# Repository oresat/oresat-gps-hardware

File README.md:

# oresat-gps-hardware 

## Overview

This is the repo for our OreSat GPS Card. For software, see the [oresat-gps-software](https://github.com/oresat/oresat-gps-software) repo.

The card has two GPS receivers on it:

* A [**SkyTraq Orion-B16** GNSS module](https://navspark.mybigcommerce.com/12mm-x-16mm-gnss-receiver-module-for-leo-applications/), a GNSS receiver module meant for university CubeSat use.
* An [Analog Devices MAX2771 SDR GNSS receiver IC](https://www.analog.com/en/products/max2771.html) that is read by the [Octavo OSD335x-SM processor's](https://octavosystems.com/octavo_products/osd335x-sm/) PRU and then parsed using the [GNSS-SDR project](https://gnss-sdr.org/) software.

## Status

TRL 6-7 ish. Flown, but not yet demonstrated to work in space.

* v1.1: Assembled, electrical and software test out, Orion not yet locked and demonstrated to work. MAX not yet tested.
* v1.0: Works: SkyTraq confirmed locked on ground. SDR datastream captured, and processed, but this software seems to be lost to the sands of time? Flown on OreSat0 but never turned on due to comms issues with OreSat0.

## License

All materials in this repo are copyright Portland State Aerospace Society and are licensed under the CERN Open Hardware Licence Version 2 -
Strongly Reciprocal (CERN-OHL-S v2), or any later version. A copy of the license is located in [here](LICENSE.md).

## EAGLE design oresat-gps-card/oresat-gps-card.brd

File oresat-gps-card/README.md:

---
title: "**OreSat GPS Card**"
subtitle: |
  **Fabrication and Assembly Information**\
  For build TIME-STAMP
fontsize: 10pt
geometry:
  - margin=0.5in
toc: true
toc-depth: 2
colorlinks: true
urlcolor: blue
---

\newpage

# About this Board

## Board Description

The OreSat GPS Card provides two GPS receivers for the OreSat bus:

1. The SkyTraq Orion B16 which is a COTS GPS receiver capable of lock while in orbit.
2. The MAX2769 SDR GPS receiver. This hardware is for a future SDR capability we'd
like to have, and might one day replace the much more expensive COTS receiver.

## Documentation Links

- GPS hardware Git repository: <https://github.com/oresat/oresat-gps-hardware>
- GPS software Git reposity: <https://github.com/oresat/oresat-gps-software>
- **TODO:** GPS Design Notes + Design Review Notes

## Documentation Files

| Filename                        | Notes                                    |
| ------------------------------- | ---------------------------------------- |
| README.pdf                      | This README file                         |
| PROJECT-NAME-outline.dxf        | Board outline (with holes) in DXF format |
| PROJECT-NAME-pcba.step          | 3D model of PCBA (with components)       |
| PROJECT-NAME-render-bot.jpg     | Render of the top of the 3D model        |
| PROJECT-NAME-render-bot.jpg     | Render of the bottom of the 3D model     |
| PROJECT-NAME-schematic.pdf      | PDF of board schematics                  |

## Contact Information

- Website: <https://www.oresat.org/>
- Email: <oresat@pdx.edu>
- Instagram: @pdxaerospace

## Board Renders

{width=50%}
{width=50%}

\newpage

# Printed Circuit Board (PCB) Fabrication Information

## Board Info

- 4 layer board
- Bounding box is 99.8 x 94.6 mm (3.93 x 3.72 in)
- Board thickness is 1.59 mm (0.063 inch)
- **Important:** See Materials and Stack Up sections below

## Board Requirements

- Design Rules
    - Minimum Trace / Space design rules
       - Outer layers: 0.127 mm (5.0 mil) / 0.127 mm (5.0 mil)
       - Inner layers: 0.127 mm (5.0 mil) / 0.127 mm (5.0 mil)
    - Outer dimension router tolerance: +/- 0.254 mm (10.0 mil)
    - Hole placement tolerance: +/- 0.075 mm (3.0 mil)
    - Inner tab routed slot tolerance: +/- 0.254 mm (10.0 mil)
- Drills
   - Drill Positional Tolerance: 0.051 mm (2.0 mil)
   - Drill Size tolerance: +/- 0.064 mm (2.5 mil)
- Plated/Un-plated holes
  - There are 6 un-plated (NPT) holes
  - There are 1477 plated through (PTH) holes
  - PTH minimum diameter: 0.254 mm (10 mil)
  - PTH minimum annulus: 0.102 mm (4 mil) radius
- Outline/Routing
  - Requires a 1.0 mm or smaller diameter routing bit
- Slots
  - There are no slots.
- Cutouts
  - There are no cutouts
- There are 3 fiducials on the top layer.
- Panel tabs ("mouse bites")
   - Card edges must be smooth; no mouse bites or other intrusions into the card outline.
   - If external mouse bites are required, minimize and customer will remove by hand before assembly.
- If not otherwise specified, build to IPC 6012 Class 2 or better.

## Materials

- Controlled impedance
   - The stackup is critical for the performance of high speed signals on this board.
   - As long as the stackup is controlled, the board is not considered controlled impedance.
- Isola FR408HR or material with equivalent Dk.
- Board Surface treatment should be ENIG, althogh immersion Silver is acceptable.
- White silkscreen on top and bottom surface
- Taiyo PSR-4000 or equivalent soldermask on top and bottom, no requirements for color.

## Stack Up

| Layer         | Thickness           | Notes                                        |
|---------------|---------------------|----------------------------------------------|
| Top Copper    | 0.043 mm /  1.7 mil |  Layer 1 foil, 1 oz Cu after plating         |
| prepreg       | 0.200 mm /  7.9 mil |  Prepreg - Isola FR408HR 2113                |
| Layer 2       | 0.018 mm /  0.7 mil |  Layer 2 foil, 0.5 oz Cu                     |
| Core          | 0.991 mm /   39 mil |  Core Isola FR408HR                          |
| Layer 3       | 0.018 mm /  0.7 mil |  Layer 3 foil, 0.5 oz Cu                     |
| prepreg       | 0.200 mm /  7.9 mil |  Prepreg - Isola FR408HR 2113                |
| Bottom Copper | 0.043 mm /  1.7 mil |  Layer 4 foil, 1 oz copper after plating     |
| **Total Stackup** | **1.588 mm / 62.5 mil** |                                      |

## Array / Panel Information

- Coordinate with Contract Manufacturer (CM) for optimal size of this panel.
- If no feedback from CM, then produce single boards (no panel).

## Fabrication Files

### IPC-2581 File

| Filename                 | Notes                                   |
| ------------------------ | --------------------------------------- |
| PROJECT-NAME-ipc2581.xml | IPC-2581 board information file         |

### Legacy PCB Files

| Filename                      | Notes                                         |
| ------------------------------| --------------------------------------------- |
| PROJECT-NAME-Edge_Cuts.gbr    | RS274X file for the dimension (outline) layer |
| PROJECT-NAME-F_Silkscreen.gbr | RS274X file for the top silkscreen            |
| PROJECT-NAME-F_Mask.gbr       | RS274X file for the top soldermask            |
| PROJECT-NAME-F_Cu.gbr         | RS274X file for the top copper layer          |
| PROJECT-NAME-In1_Cu.gbr       | RS274X file for the layer 2 copper            |
| PROJECT-NAME-In2_Cu.gbr       | RS274X file for the layer 3 copper            |
| PROJECT-NAME-B_Cu.gbr         | RS274X file for the bottom copper layer       |
| PROJECT-NAME-B_Mask.gbr       | RS274X file for the bottom soldermask         |
| PROJECT-NAME-B_Silkscreen.gbr | RS274X file for the bottom silkscreen         |
| PROJECT-NAME-NPTH.drl         | Excellon file for non-plated through holes    |
| PROJECT-NAME-PTH.drl          | Excellon file for plated through holes        | 

\newpage

# Printed Circuit Board Assembly (PCBA) Information

## Assembly Info

- All components are on the top side of the board.
- This PCBA is mostly surface mount (SMT) with a few (THT) components.

## Assembly Requirements

- Assemble to IPC Class 2 or better
- Bake components that are not moisture sealed to appropriate levels as required.
- Solder paste MUST be leaded.
- Aqueous flux and wash strongly preferred.
   - Clean to NASA Standard "Visibly Clean (VC)": No particles or residues are visible to the naked eye.
- No conformal coating.
- Ship in antistatic protective bag

## Component Specific Assembly Information

- SMPM connectors (CM1) should be hand-added (there is no solder paste for their footprints) according to the OreSat SMPM SOP.
- U23 is extremely expensive ($400 ea).

## Assembly Files

### IPC-2581 File

| Filename                 | Notes                           |
| ------------------------ | ------------------------------- |
| PROJECT-NAME-ipc2581.xml | IPC-2581 board information file |

### Bill of Materials (BOM)

| Filename             | Description                            |
| -------------------- | -------------------------------------- |
| PROJECT-NAME-bom.csv | BOM in Comma Separated Variable format |

### Solder Paste Stencils

| Filename                 | Notes                                            |
| ------------------------ | ------------------------------------------------ |
| PROJECT-NAME-B_Paste.gbr | RS274X file for top/front solder paste stencil   |
| PROJECT-NAME-F_Paste.gbr | RS274X file for bottom/back solder paste stencil |

### Mounting/Placement Location

| Filename            | Description                                 |
| ------------------- | ------------------------------------------- |
| PROJECT-NAME-3u.pos | Pick and place locations for components     |

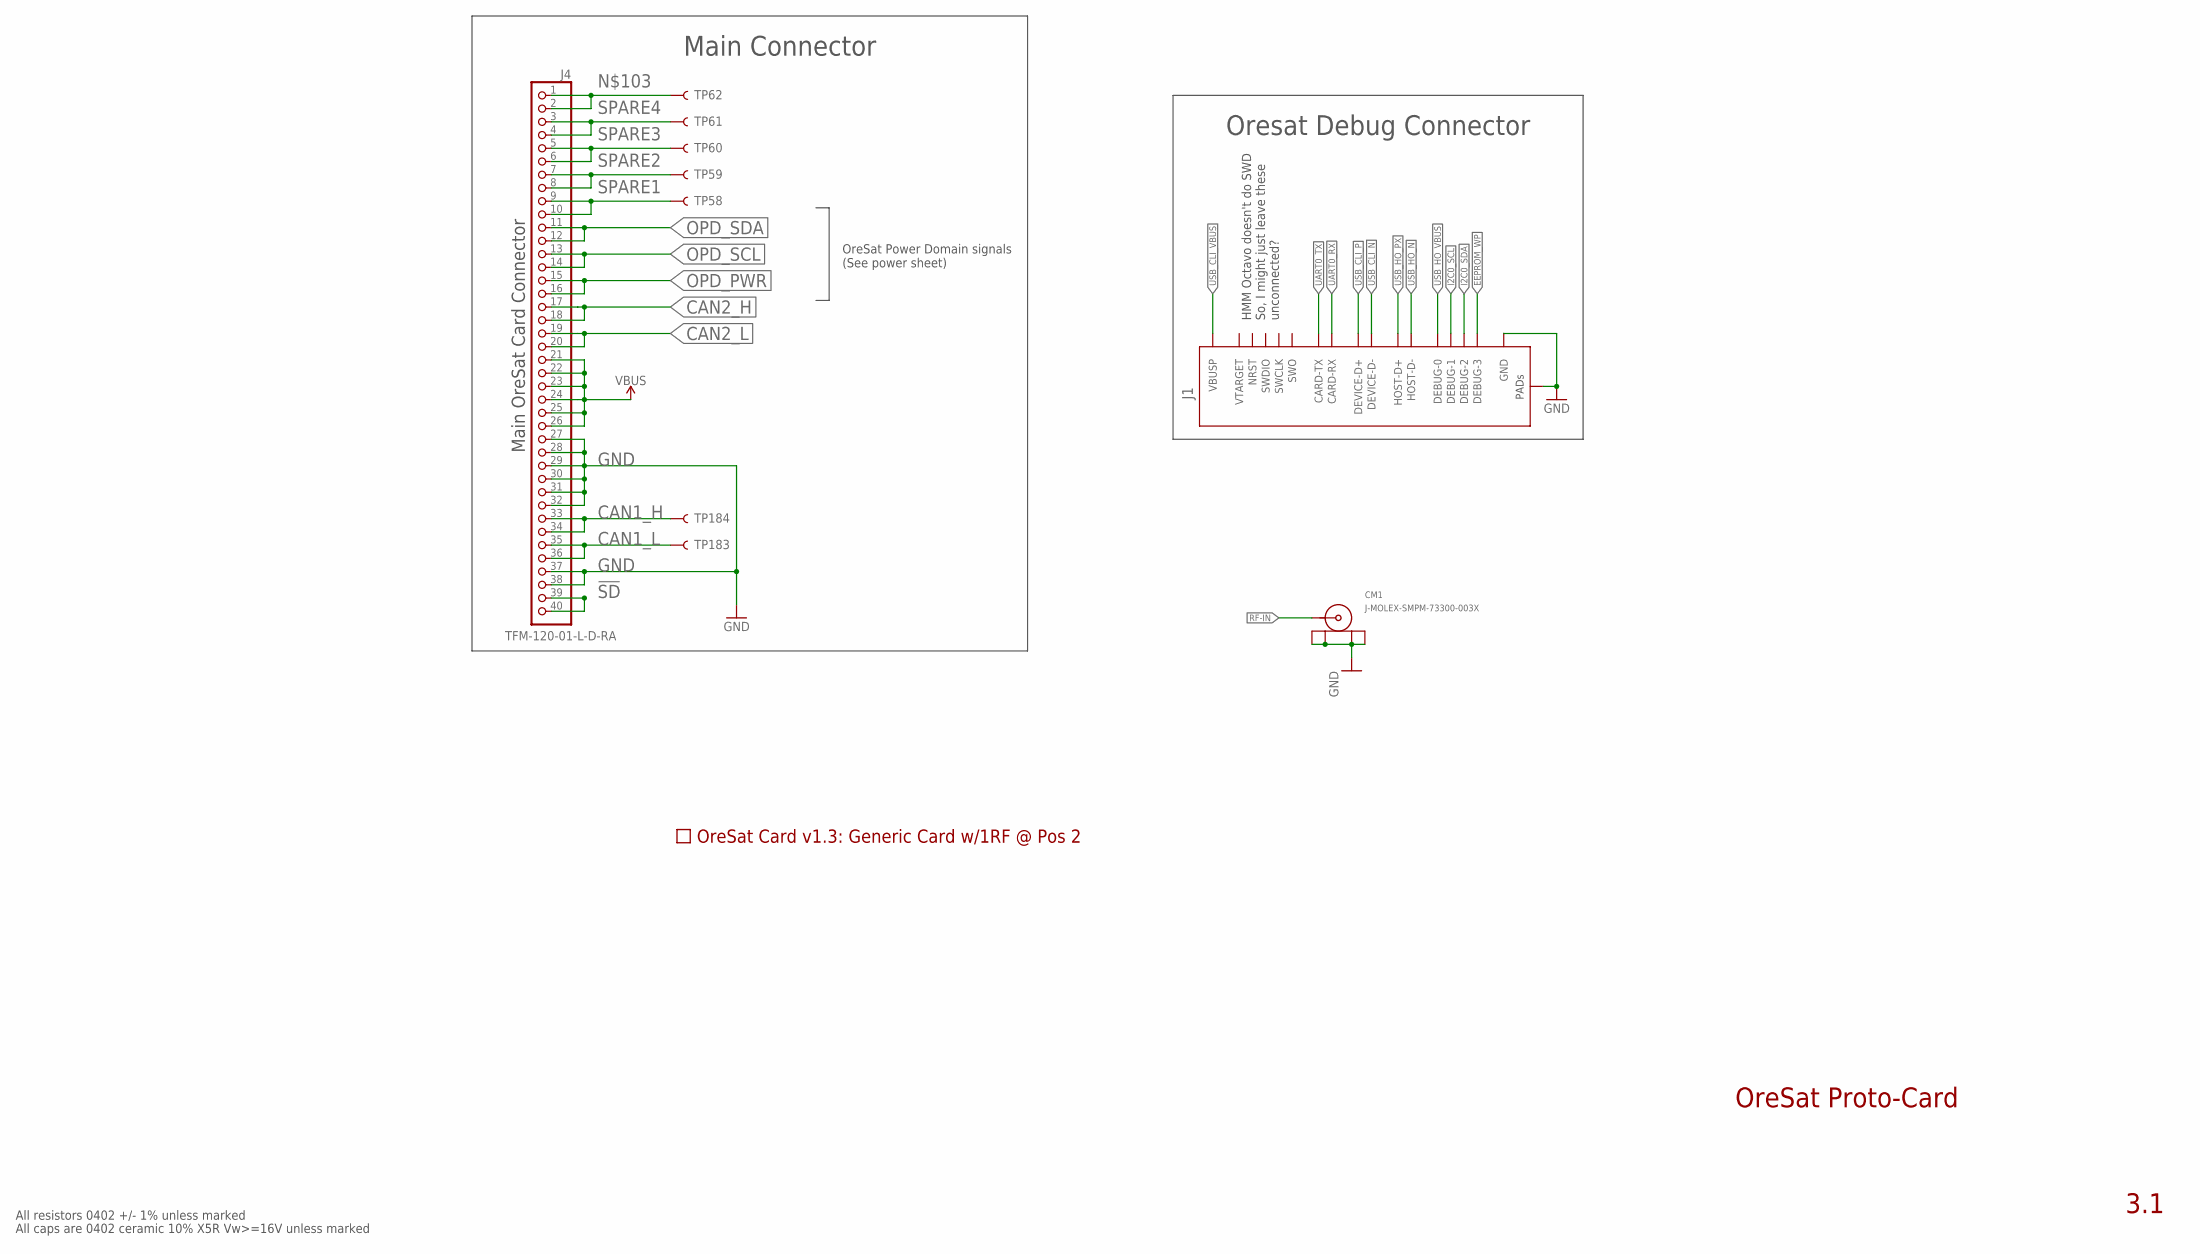
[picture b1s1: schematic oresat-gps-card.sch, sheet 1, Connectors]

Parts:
CM1: J-MOLEX-SMPM-73300-003X; J-MOLEX-SMPM-073300-003X
J1: ORESAT-DEBUG-CONNECTOR-CARD; TE_2-1734592-0
J4: TFM-120-01-L-D-RA; J-SAMTEC-TFM-120-X1-XXX-D-RA
PCB1: ORESAT-CARD-V1.3-GENERIC-1RF-POS2
TP58, TP59, TP60, TP61, TP62, TP183, TP184: TEST-POINT3X4; PAD.03X.04

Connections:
!SD: J4.39, J4.40
CAN1_H: J4.33, J4.34, TP184.P$1
CAN1_L: J4.35, J4.36, TP183.P$1
CAN2_H: J4.17, J4.18; also elsewhere on the board
CAN2_L: J4.19, J4.20; also elsewhere on the board
EEPROM_WP: J1.20 (DEBUG-3); also elsewhere on the board
GND: CM1.P$1 (SHIELD3), CM1.P$2 (SHIELD2), CM1.P$3 (SHIELD1), CM1.P$4 (SHIELD), J1.3 (GND), J1.6 (GND), J1.9 (GND), J1.PAD1 (PAD), J1.PAD2 (PAD), J4.27, J4.28, J4.29, J4.30, J4.31, J4.32, J4.37, J4.38; also elsewhere on the board
I2C0_SCL: J1.18 (DEBUG-1); also elsewhere on the board
I2C0_SDA: J1.19 (DEBUG-2); also elsewhere on the board
unnamed: J4.1, J4.2, TP62.P$1
OPD_PWR: J4.15, J4.16; also elsewhere on the board
OPD_SCL: J4.13, J4.14; also elsewhere on the board
OPD_SDA: J4.11, J4.12; also elsewhere on the board
RF-IN: CM1.RF (CENTER); also elsewhere on the board
SPARE1: J4.9, J4.10, TP58.P$1
SPARE2: J4.7, J4.8, TP59.P$1
SPARE3: J4.5, J4.6, TP60.P$1
SPARE4: J4.3, J4.4, TP61.P$1
UART0_RX: J1.12 (CARD-RX); also elsewhere on the board
UART0_TX: J1.13 (CARD-TX); also elsewhere on the board
USB_CLI_N: J1.5 (DEVICE-D-); also elsewhere on the board
USB_CLI_P: J1.4 (DEVICE-D+); also elsewhere on the board
USB_CLI_VBUS: J1.1 (VBUSP), J1.2 (VBUSP); also elsewhere on the board
USB_HO_N: J1.8 (HOST-D-); also elsewhere on the board
USB_HO_PX: J1.7 (HOST-D+); also elsewhere on the board
USB_HO_VBUS: J1.17 (DEBUG-0); also elsewhere on the board
VBUS: J4.21, J4.22, J4.23, J4.24, J4.25, J4.26; also elsewhere on the board

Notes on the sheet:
OreSat Proto-Card
3.1
All resistors 0402 +/- 1% unless marked
All caps are 0402 ceramic 10% X5R Vw>=16V unless marked
Main Connector
Main OreSat Card Connector
OreSat Power Domain signals (See power sheet)
HMM Octavo doesn't do SWD So, I might just leave these unconnected?
Oresat Debug Connector

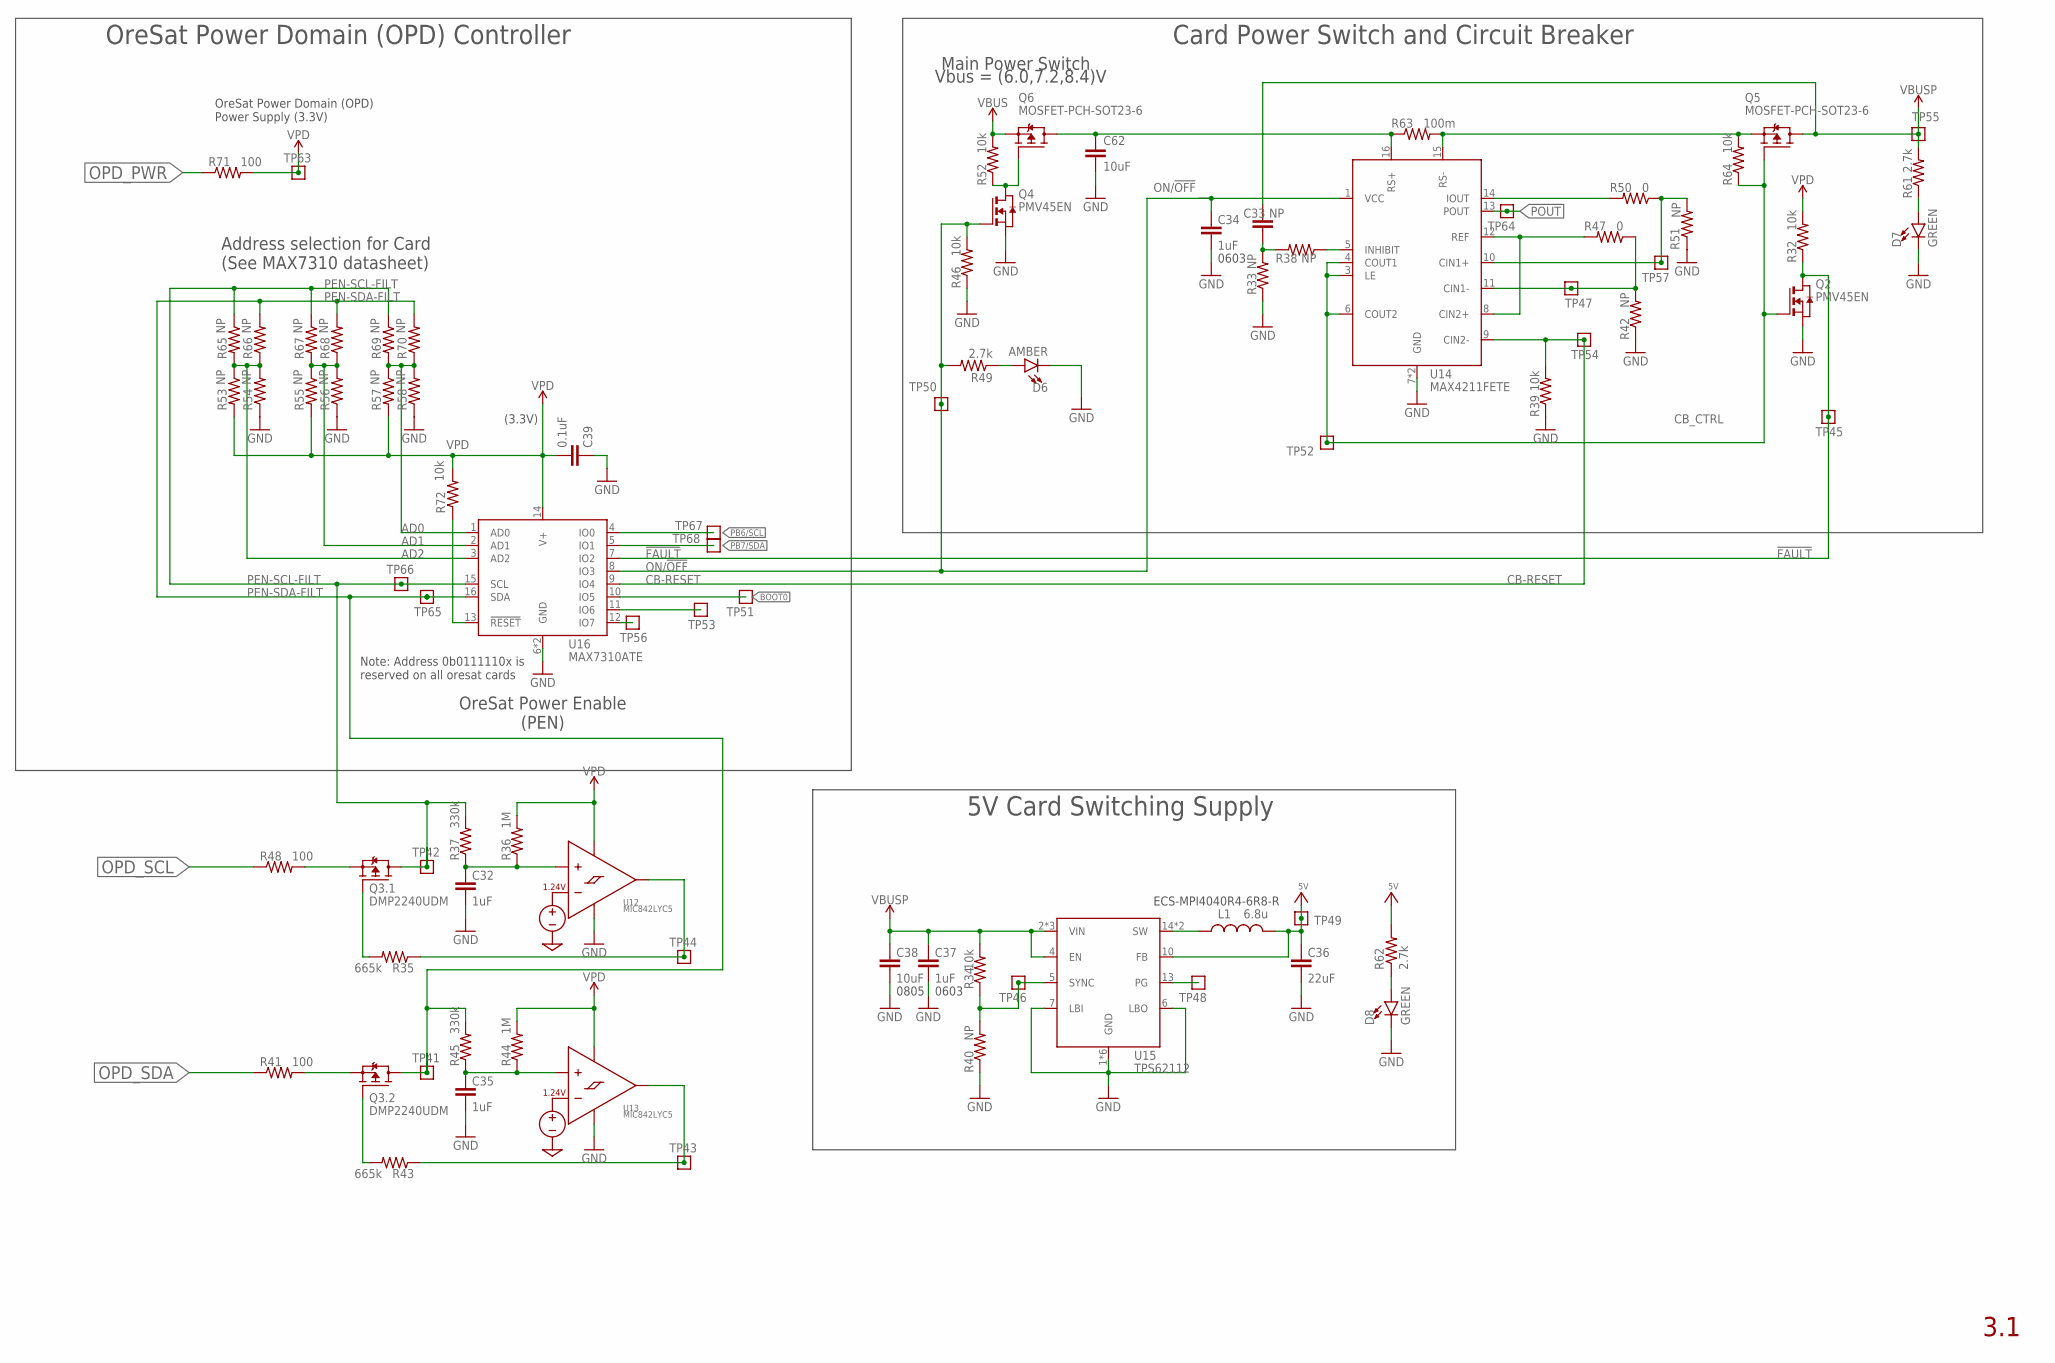
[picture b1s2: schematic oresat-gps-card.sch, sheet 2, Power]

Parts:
C32, C35: 1uF; .0805-B-NOSILK
C33: NP; .0603-A; MPN CL05B104KO5NNNC
C34, C37: 1uF; .0603-A
C36: 22uF; C1210
C38, C62: 10uF; .0805-B
C39: 0.1uF; .0603-A
D6: AMBER; LED-0603
D7, D8: GREEN; LED-0603
L1: 6.8u; ECS-MPI4040
Q2, Q4: PMV45EN; SOT23; MPN PMV45EN2R
Q3: DMP2240UDM; SOT23-6
Q5, Q6: MOSFET-PCH-SOT23-6; SOT23-6; MPN DMP3050LVT-7
R32, R34, R39, R46, R52, R64, R72: 10k; .0603-A
R33, R38, R40, R42, R51, R53, R54, R55, R56, R57, R58, R65, R66, R67, R68, R69, R70: NP; .0603-A; MPN RC1005F6653CS
R35, R43: 665k; .0603-A
R36, R44: 1M; .0603-A
R37, R45: 330k; .0603-A
R41, R48, R71: 100; .0603-A
R47, R50: 0; .0603-A
R49, R61, R62: 2.7k; .0603-A
R63: 100m; R1206
TP41, TP42, TP43, TP44, TP45, TP46, TP47, TP48, TP49, TP50, TP51, TP52, TP53, TP54, TP55, TP56, TP57, TP63, TP64, TP65, TP66, TP67, TP68: TEST-POINT; 2MM-TEST-POINT
U12, U13: MIC842LYC5; SC70-5
U14: MAX4211FETE; QFN65P400X400X80-17T210
U15: TPS62112; S-PVQFN-16
U16: MAX7310ATE; QFN65P400X400X80-17T210; MPN MAX7310ATE

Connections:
5V: C36.1, L1.2, R62.2, TP49.1, U15.10 (FB); also elsewhere on the board
!FAULT: Q2.3 (D), R32.1, TP45.1, U16.7 (IO2)
AD0: R57.1, R58.2, R69.2, R70.1, U16.1 (AD0)
AD1: R55.1, R56.2, R67.2, R68.1, U16.2 (AD1)
AD2: R53.1, R54.2, R65.2, R66.1, U16.3 (AD2)
BOOT0: TP51.1, U16.10 (IO5)
CB-RESET: R39.2, TP54.1, U14.9 (CIN2-), U16.9 (IO4)
CB_CTRL: Q2.1 (G), Q5.3 (G), R64.1, TP52.1, U14.3 (LE), U14.4 (COUT1), U14.6 (COUT2)
GND: C32.2, C34.2, C35.2, C36.2, C37.2, C38.2, C39.1, C62.2, D6.C, D7.C, D8.C, Q2.2 (S), Q4.2 (S), R33.1, R39.1, R40.1, R42.1, R46.1, R51.1, R54.1, R56.1, R58.1, U12.2 (GND), U13.2 (GND), U14.7 (GND), U14.EPAD (GND), U15.1 (GND), U15.6 (LBO), U15.7 (LBI), U15.9 (GND), U15.11 (GND), U15.12 (GND), U15.16 (GND), U15.PAD (GND), U16.6 (GND), U16.EPAD (GND); also elsewhere on the board
IOUT: R50.2, U14.14 (IOUT)
unnamed: C32.1, R36.1, R37.1, U12.1 (INP)
unnamed: R35.1, TP44.1, U12.4 (OUT)
unnamed: C62.1, Q6.1 (D), Q6.2 (D), Q6.5 (D), Q6.6 (D), R63.1, U14.16 (RS+)
unnamed: Q5.4 (S), R63.2, R64.2, U14.15 (RS-)
unnamed: C35.1, R44.1, R45.1, U13.1 (INP)
unnamed: Q3.3 (G), R43.2
unnamed: Q3.1 (G), R35.2
unnamed: TP56.1, U16.12 (IO7)
unnamed: D7.A, R61.1
unnamed: D8.A, R62.1
unnamed: TP53.1, U16.11 (IO6)
unnamed: Q3.5 (S), R48.2
unnamed: D6.A, R49.1
unnamed: Q3.2 (S), R41.2
unnamed: R43.1, TP43.1, U13.4 (OUT)
unnamed: R72.1, U16.13 (!RESET)
unnamed: Q4.3 (D), Q6.3 (G), R52.1
unnamed: R50.1, R51.2, TP57.1, U14.10 (CIN1+)
unnamed: R42.2, R47.1, TP47.1, U14.11 (CIN1-)
unnamed: R47.2, U14.8 (CIN2+), U14.12 (REF)
unnamed: C33.1, R33.2, R38.2
unnamed: R38.1, U14.5 (INHIBIT)
ON/!OFF: C34.1, Q4.1 (G), R46.2, R49.2, TP50.1, U14.1 (VCC), U16.8 (IO3)
OPD_PWR: R71.1; also elsewhere on the board
OPD_SCL: R48.1; also elsewhere on the board
OPD_SDA: R41.1; also elsewhere on the board
PB6/SCL: TP67.1, U16.4 (IO0)
PB7/SDA: TP68.1, U16.5 (IO1)
PEN-SCL-FILT: Q3.6 (D), R37.2, R65.1, R67.1, R69.1, TP42.1, TP66.1, U16.15 (SCL)
PEN-SDA-FILT: Q3.4 (D), R45.2, R66.2, R68.2, R70.2, TP41.1, TP65.1, U16.16 (SDA)
POUT: TP64.1, U14.13 (POUT)
TPS62111-PG: TP48.1, U15.13 (PG)
TPS62111-SYNC: R34.1, R40.2, TP46.1, U15.5 (SYNC)
TPS62111_SW: L1.1, U15.14 (SW), U15.15 (SW)
VBUS: Q6.4 (S), R52.2; also elsewhere on the board
VBUSP: C33.2, C37.1, C38.1, Q5.1 (D), Q5.2 (D), Q5.5 (D), Q5.6 (D), R34.2, R61.2, TP55.1, U15.2 (VIN), U15.3 (VIN), U15.4 (EN), U15.8 (VIN)
VPD: C39.2, R32.2, R36.2, R44.2, R53.2, R55.2, R57.2, R71.2, R72.2, TP63.1, U12.5 (VDD), U13.5 (VDD), U16.14 (V+)

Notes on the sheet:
0805
0603
ECS-MPI4040R4-6R8-R
5V Card Switching Supply
3.1
Main Power Switch
OreSat Power Enable (PEN)
Address selection for Card (See MAX7310 datasheet)
(3.3V)
Vbus = (6.0,7.2,8.4)V
OreSat Power Domain (OPD) Power Supply (3.3V)
OreSat Power Domain (OPD) Controller
Card Power Switch and Circuit Breaker
Note: Address 0b0111110x is reserved on all oresat cards

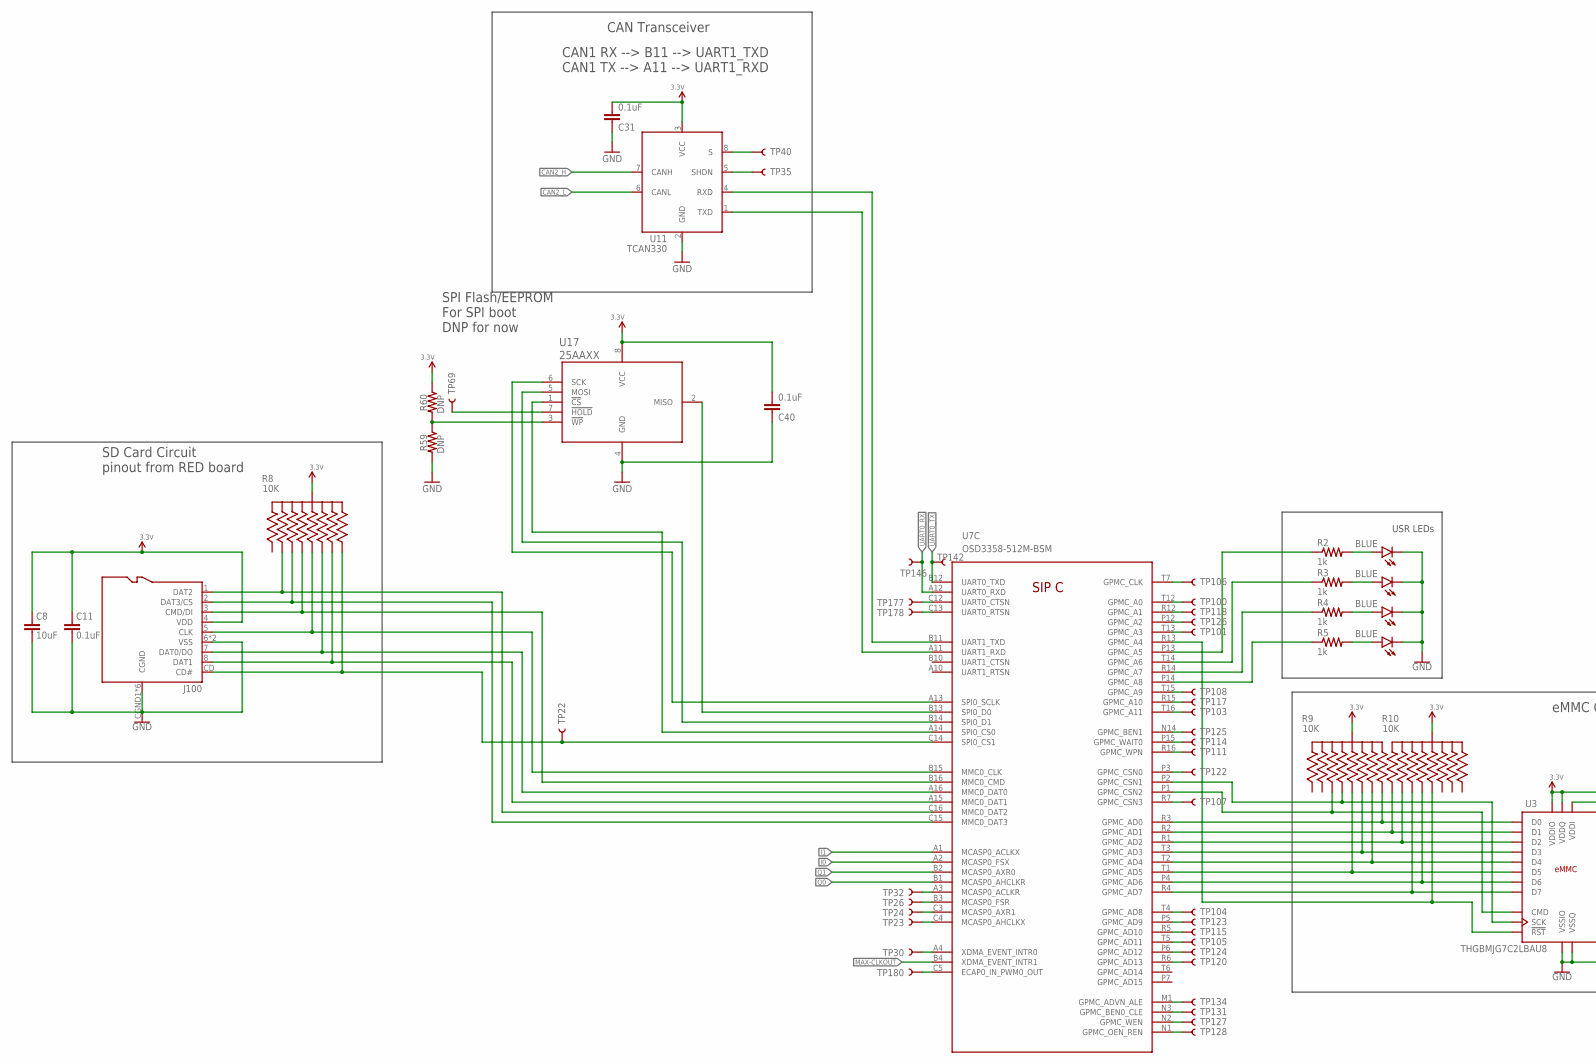
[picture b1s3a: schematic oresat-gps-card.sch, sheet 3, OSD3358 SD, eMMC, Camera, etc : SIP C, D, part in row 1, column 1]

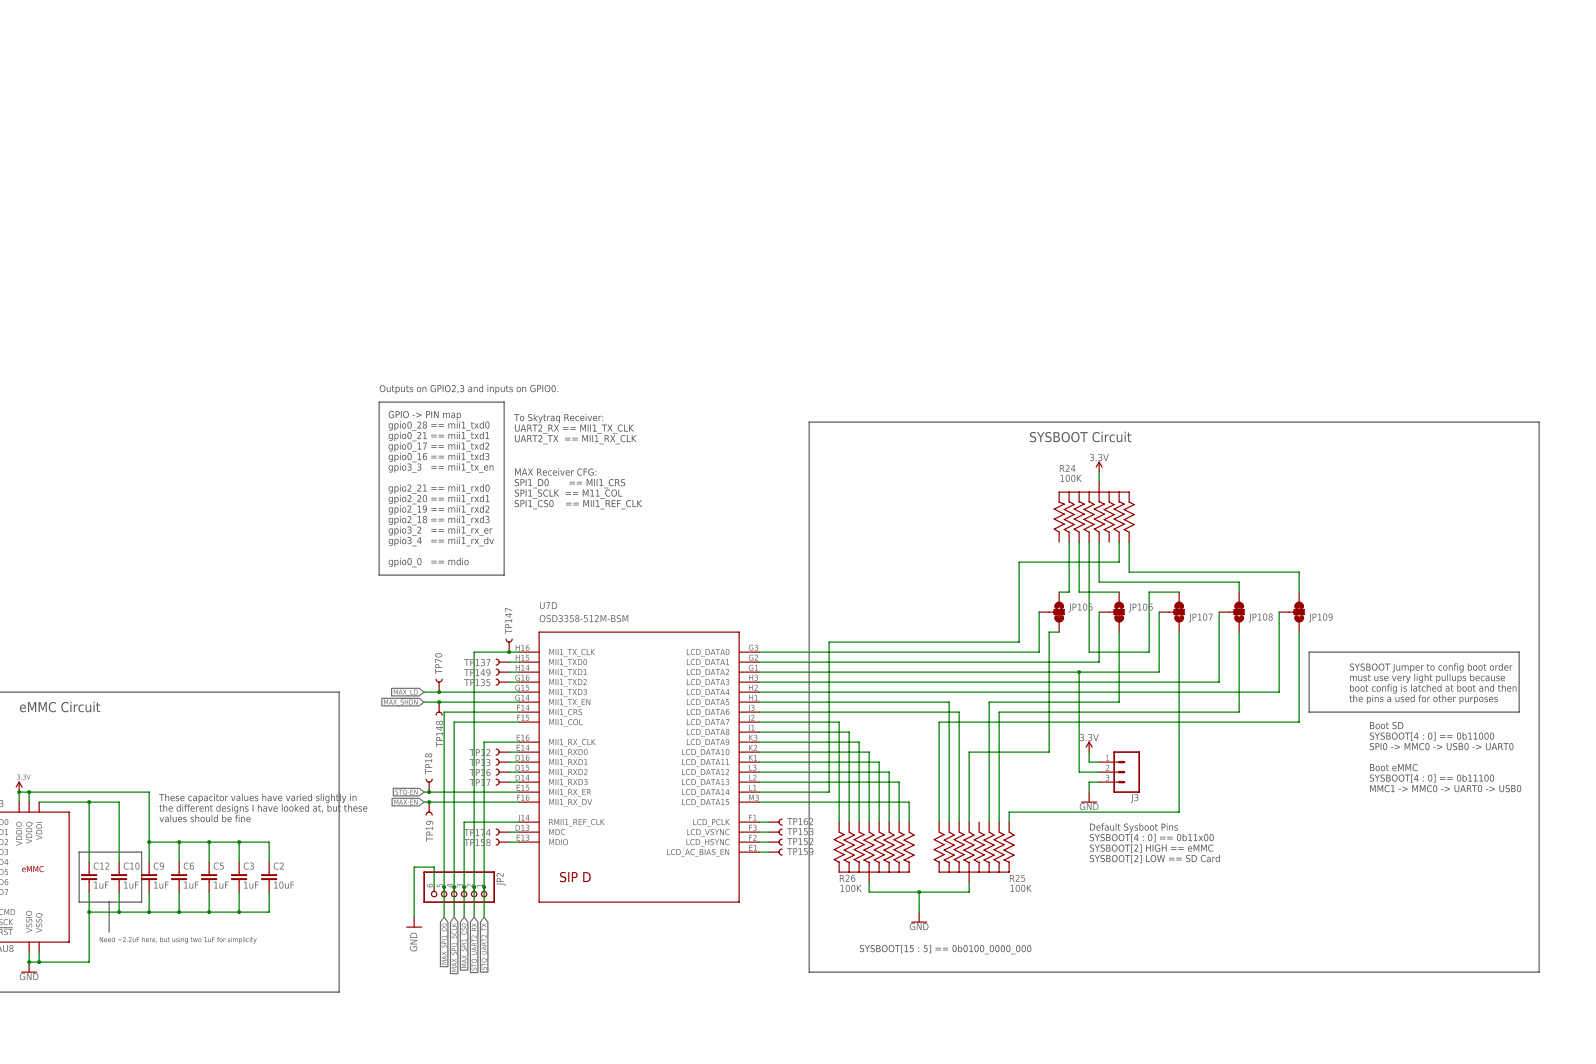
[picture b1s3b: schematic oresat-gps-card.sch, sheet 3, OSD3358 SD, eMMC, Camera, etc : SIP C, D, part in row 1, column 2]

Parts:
C2, C8: 10uF; .0805-B
C3, C5, C6, C9, C10, C12: 1uF; .0603-A
C11, C31, C40: 0.1uF; .0603-A
D2, D3, D4, D5: BLUE; LED-0603
J3: CONN_03LONGPADS; 1X03_LONGPADS
J100: DM3BT-DSF-PEJS
JP2: PINHD-1X6; 1X06
JP105, JP106, JP107, JP108, JP109: JUMPER-SMT_3_1-NC_TRACE_SILK; SMT-JUMPER_3_1-NC_TRACE_SILK
R2, R3, R4, R5: 1k; .0603-A
R8, R9, R10: 10K; ARRAY_EXBA-M; MPN EXB-A10P103J
R24, R25, R26: 100K; ARRAY_EXBA-M; MPN EXB-A10P104J
R59, R60: DNP; .0603-A
TP12, TP13, TP16, TP17, TP18, TP19, TP22, TP23, TP24, TP26, TP30, TP32, TP35, TP40, TP69, TP70, TP100, TP101, TP103, TP104, TP105, TP106, TP107, TP108, TP111, TP114, TP115, TP117, TP118, TP120, TP122, TP123, TP124, TP125, TP126, TP127, TP128, TP131, TP134, TP135, TP137, TP142, TP146, TP147, TP148, TP149, TP152, TP153, TP158, TP159, TP162, TP174, TP177, TP178, TP180: TEST-POINT3X4; PAD.03X.04
U3: THGBMJG7C2LBAU8; BGA-153(11.5X13)(EMMC-BA); MPN THGBMJG7C2LBAU8
U7: OSD3358-512M-BSM; OSD335X-BGA-256
U11: TCAN330; SOT23-8_TI-DCN
U17: 25AAXX; SOIC8

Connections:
3.3V: C2.1, C3.1, C5.1, C6.1, C8.1, C9.1, C11.1, C31.2, C40.2, J3.1, J100.4 (VDD), R8.5 (55), R8.10 (55), R9.5 (55), R9.10 (55), R10.5 (55), R10.10 (55), R24.5 (55), R24.10 (55), R60.1, U3.C6 (VDDQ), U3.E6 (VDDIO), U3.F5 (VDDIO), U3.J10 (VDDIO), U3.K9 (VDDIO), U3.M4 (VDDQ), U3.N4 (VDDQ), U3.P3 (VDDQ), U3.P5 (VDDQ), U11.3 (VCC), U17.8 (VCC); also elsewhere on the board
CAN2_H: U11.7 (CANH); also elsewhere on the board
CAN2_L: U11.6 (CANL); also elsewhere on the board
GND: C2.2, C3.2, C5.2, C6.2, C8.2, C9.2, C10.2, C11.2, C12.2, C31.1, C40.1, D2.C, D3.C, D4.C, D5.C, J3.3, J100.6 (VSS), J100.CGND1 (CGND), J100.CGND2 (CGND), J100.CGND3 (CGND), J100.CGND4 (CGND), J100.CGND5 (CGND), J100.CGND6 (CGND), J100.GND (VSS), JP2.6, R25.5 (55), R25.10 (55), R26.5 (55), R26.10 (55), R59.2, U3.C4 (VSSQ), U3.E7 (VSSIO), U3.G5 (VSSIO), U3.H10 (VSSIO), U3.J5 (VSSIO), U3.K8 (VSSIO), U3.N2 (VSSQ), U3.N5 (VSSQ), U3.P4 (VSSQ), U3.P6 (VSSQ), U11.2 (GND), U17.4 (GND); also elsewhere on the board
I0: U7.A2 (MCASP0_FSX); also elsewhere on the board
I1: U7.A1 (MCASP0_ACLKX); also elsewhere on the board
MAX-CLKOUT: U7.B4 (XDMA_EVENT_INTR1); also elsewhere on the board
MAX-EN: TP19.P$1, U7.F16 (MII1_RX_DV); also elsewhere on the board
MAX_!SHDN: TP148.P$1, U7.G14 (MII1_TX_EN); also elsewhere on the board
MAX_LD: TP70.P$1, U7.G15 (MII1_TXD3); also elsewhere on the board
MAX_SPI1_CS0: JP2.3, U7.J14 (RMII1_REF_CLK); also elsewhere on the board
MAX_SPI1_D0: JP2.5, U7.F14 (MII1_CRS); also elsewhere on the board
MAX_SPI1_SCLK: JP2.4, U7.F15 (MII1_COL); also elsewhere on the board
unnamed: D5.A, R5.2
unnamed: J100.1 (DAT2), R8.9 (99), U7.C16 (MMC0_DAT2)
unnamed: J100.2 (DAT3/CS), R8.2 (22), U7.C15 (MMC0_DAT3)
unnamed: J100.3 (CMD/DI), R8.8 (88), U7.B16 (MMC0_CMD)
unnamed: J100.5 (CLK), R8.3 (33), U7.B15 (MMC0_CLK)
unnamed: J100.7 (DAT0/DO), R8.7 (77), U7.A16 (MMC0_DAT0)
unnamed: J100.8 (DAT1), R8.4 (44), U7.A15 (MMC0_DAT1)
unnamed: J100.CD (CD#), R8.6 (66), TP22.P$1, U7.C14 (SPI0_CS1)
unnamed: U7.B11 (UART1_TXD), U11.4 (RXD)
unnamed: U7.A11 (UART1_RXD), U11.1 (TXD)
unnamed: TP40.P$1, U11.8 (S)
unnamed: TP35.P$1, U11.5 (SHDN)
unnamed: TP23.P$1, U7.C4 (MCASP0_AHCLKX)
unnamed: TP24.P$1, U7.C3 (MCASP0_AXR1)
unnamed: TP26.P$1, U7.B3 (MCASP0_FSR)
unnamed: TP32.P$1, U7.A3 (MCASP0_ACLKR)
unnamed: U7.A13 (SPI0_SCLK), U17.6 (SCK)
unnamed: U7.B13 (SPI0_D0), U17.2 (MISO)
unnamed: U7.B14 (SPI0_D1), U17.5 (MOSI)
unnamed: U7.A14 (SPI0_CS0), U17.1 (!CS)
unnamed: TP30.P$1, U7.A4 (XDMA_EVENT_INTR0)
unnamed: TP180.P$1, U7.C5 (ECAP0_IN_PWM0_OUT)
unnamed: TP104.P$1, U7.T4 (GPMC_AD8)
unnamed: TP123.P$1, U7.P5 (GPMC_AD9)
unnamed: TP115.P$1, U7.R5 (GPMC_AD10)
unnamed: TP105.P$1, U7.T5 (GPMC_AD11)
unnamed: TP124.P$1, U7.P6 (GPMC_AD12)
unnamed: TP120.P$1, U7.R6 (GPMC_AD13)
unnamed: TP125.P$1, U7.N14 (GPMC_BEN1)
unnamed: TP114.P$1, U7.P15 (GPMC_WAIT0)
unnamed: TP111.P$1, U7.R16 (GPMC_WPN)
unnamed: TP177.P$1, U7.C12 (UART0_CTSN)
unnamed: TP178.P$1, U7.C13 (UART0_RTSN)
unnamed: TP162.P$1, U7.F1 (LCD_PCLK)
unnamed: TP153.P$1, U7.F3 (LCD_VSYNC)
unnamed: TP152.P$1, U7.F2 (LCD_HSYNC)
unnamed: TP159.P$1, U7.E1 (LCD_AC_BIAS_EN)
unnamed: TP174.P$1, U7.D13 (MDC)
unnamed: TP158.P$1, U7.E13 (MDIO)
unnamed: TP12.P$1, U7.E14 (MII1_RXD0)
unnamed: TP137.P$1, U7.H15 (MII1_TXD0)
unnamed: TP149.P$1, U7.H14 (MII1_TXD1)
unnamed: TP135.P$1, U7.G16 (MII1_TXD2)
unnamed: TP106.P$1, U7.T7 (GPMC_CLK)
unnamed: TP100.P$1, U7.T12 (GPMC_A0)
unnamed: TP118.P$1, U7.R12 (GPMC_A1)
unnamed: TP126.P$1, U7.P12 (GPMC_A2)
unnamed: TP101.P$1, U7.T13 (GPMC_A3)
unnamed: D4.A, R4.2
unnamed: D3.A, R3.2
unnamed: TP108.P$1, U7.T15 (GPMC_A9)
unnamed: TP117.P$1, U7.R15 (GPMC_A10)
unnamed: TP103.P$1, U7.T16 (GPMC_A11)
unnamed: TP122.P$1, U7.P3 (GPMC_CSN0)
unnamed: TP107.P$1, U7.R7 (GPMC_CSN3)
unnamed: D2.A, R2.2
unnamed: TP134.P$1, U7.M1 (GPMC_ADVN_ALE)
unnamed: TP131.P$1, U7.N3 (GPMC_BEN0_CLE)
unnamed: TP127.P$1, U7.N2 (GPMC_WEN)
unnamed: TP128.P$1, U7.N1 (GPMC_OEN_REN)
unnamed: JP105.1, R24.9 (99)
unnamed: JP106.1, R24.2 (22)
unnamed: JP108.3, R24.3 (33)
unnamed: JP109.3, R24.6 (66)
unnamed: JP107.3, R24.8 (88)
unnamed: R59.1, R60.2, U17.3 (!WP)
unnamed: TP69.P$1, U17.7 (!HOLD)
unnamed: TP13.P$1, U7.D16 (MII1_RXD1)
unnamed: TP16.P$1, U7.D15 (MII1_RXD2)
unnamed: TP17.P$1, U7.D14 (MII1_RXD3)
unnamed: JP105.2, U7.G3 (LCD_DATA0)
unnamed: JP106.2, U7.G2 (LCD_DATA1)
unnamed: J3.2, JP107.2, U7.G1 (LCD_DATA2)
unnamed: JP108.2, U7.H3 (LCD_DATA3)
unnamed: JP109.2, U7.H2 (LCD_DATA4)
unnamed: R25.4 (44), U7.H1 (LCD_DATA5)
unnamed: R25.7 (77), U7.J3 (LCD_DATA6)
unnamed: R26.4 (44), U7.J1 (LCD_DATA8)
unnamed: R26.7 (77), U7.K3 (LCD_DATA9)
unnamed: R26.3 (33), U7.K2 (LCD_DATA10)
unnamed: R26.8 (88), U7.K1 (LCD_DATA11)
unnamed: R26.2 (22), U7.L3 (LCD_DATA12)
unnamed: R26.9 (99), U7.L2 (LCD_DATA13)
unnamed: R24.4 (44), U7.L1 (LCD_DATA14)
unnamed: R26.1 (11), U7.M3 (LCD_DATA15)
unnamed: R26.6 (66), U7.J2 (LCD_DATA7)
unnamed: JP109.1, R25.6 (66)
unnamed: JP107.1, R25.1 (11)
unnamed: JP108.1, R25.9 (99)
unnamed: JP106.3, R25.2 (22)
unnamed: JP105.3, R25.3 (33)
unnamed: C10.1, C12.1, U3.C2 (VDDI)
unnamed: R9.6 (66), U3.A3 (D0), U7.R3 (GPMC_AD0)
unnamed: R10.1 (11), U3.A4 (D1), U7.R2 (GPMC_AD1)
unnamed: R10.9 (99), U3.A5 (D2), U7.R1 (GPMC_AD2)
unnamed: R9.7 (77), U3.B2 (D3), U7.T3 (GPMC_AD3)
unnamed: R9.4 (44), U3.B3 (D4), U7.T2 (GPMC_AD4)
unnamed: R9.3 (33), U3.B4 (D5), U7.T1 (GPMC_AD5)
unnamed: R10.8 (88), U3.B5 (D6), U7.P4 (GPMC_AD6)
unnamed: R10.2 (22), U3.B6 (D7), U7.R4 (GPMC_AD7)
unnamed: R9.2 (22), U3.M5 (CMD), U7.P1 (GPMC_CSN2)
unnamed: R9.8 (88), U3.M6 (SCK), U7.P2 (GPMC_CSN1)
unnamed: R10.3 (33), U3.K5 (!RST!), U7.R13 (GPMC_A4)
unnamed: R2.1, U7.P13 (GPMC_A5)
unnamed: R3.1, U7.T14 (GPMC_A6)
unnamed: R4.1, U7.R14 (GPMC_A7)
unnamed: R5.1, U7.P14 (GPMC_A8)
Q0: U7.B1 (MCASP0_AHCLKR); also elsewhere on the board
Q1: U7.B2 (MCASP0_AXR0); also elsewhere on the board
STQ-EN: TP18.P$1, U7.E15 (MII1_RX_ER); also elsewhere on the board
STQ_UART2_RX: JP2.2, TP147.P$1, U7.H16 (MII1_TX_CLK); also elsewhere on the board
STQ_UART2_TX: JP2.1, U7.E16 (MII1_RX_CLK); also elsewhere on the board
UART0_RX: TP146.P$1, U7.A12 (UART0_RXD); also elsewhere on the board
UART0_TX: TP142.P$1, U7.B12 (UART0_TXD); also elsewhere on the board

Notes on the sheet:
SYSBOOT Jumper to config boot order must use very light pullups because boot config is latched at boot and then the pins a used for other purposes
SYSBOOT[15 : 5] == 0b0100_0000_000
Boot SD SYSBOOT[4 : 0] == 0b11000 SPI0 -> MMC0 -> USB0 -> UART0 Boot eMMC SYSBOOT[4 : 0] == 0b11100 MMC1 -> MMC0 -> UART0 -> USB0
USR LEDs
These capacitor values have varied slightly in the different designs I have looked at, but these values should be fine
eMMC Circuit
SD Card Circuit pinout from RED board
SYSBOOT Circuit
CAN Transceiver
CAN1 RX --> B11 --> UART1_TXD CAN1 TX --> A11 --> UART1_RXD
GPIO -> PIN map gpio0_28 == mii1_txd0 gpio0_21 == mii1_txd1 gpio0_17 == mii1_txd2 gpio0_16 == mii1_txd3 gpio3_3 == mii1_tx_en gpio2_21 == mii1_rxd0 gpio2_20 == mii1_rxd1 gpio2_19 == mii1_rxd2 gpio2_18 == mii1_rxd3 gpio3_2 == mii1_rx_er gpio3_4 == mii1_rx_dv gpio0_0 == mdio
Outputs on GPIO2,3 and inputs on GPIO0.
Need ~2.2uF here, but using two 1uF for simplicity
Default Sysboot Pins SYSBOOT[4 : 0] == 0b11x00 SYSBOOT[2] HIGH == eMMC SYSBOOT[2] LOW == SD Card
SPI Flash/EEPROM For SPI boot DNP for now
To Skytraq Receiver: UART2_RX == MII1_TX_CLK UART2_TX == MII1_RX_CLK
MAX Receiver CFG: SPI1_D0 == MII1_CRS SPI1_SCLK == M11_COL SPI1_CS0 == MII1_REF_CLK

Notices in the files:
parts and their libraries:
SparkFun-LED: Licensing: Creative Commons ShareAlike 4.0 International - https://creativecommons.org/licenses/by-sa/4.0
SparkFun-PowerIC: Licensing: CC v3.0 Share-Alike You are welcome to use this library for commercial purposes.
